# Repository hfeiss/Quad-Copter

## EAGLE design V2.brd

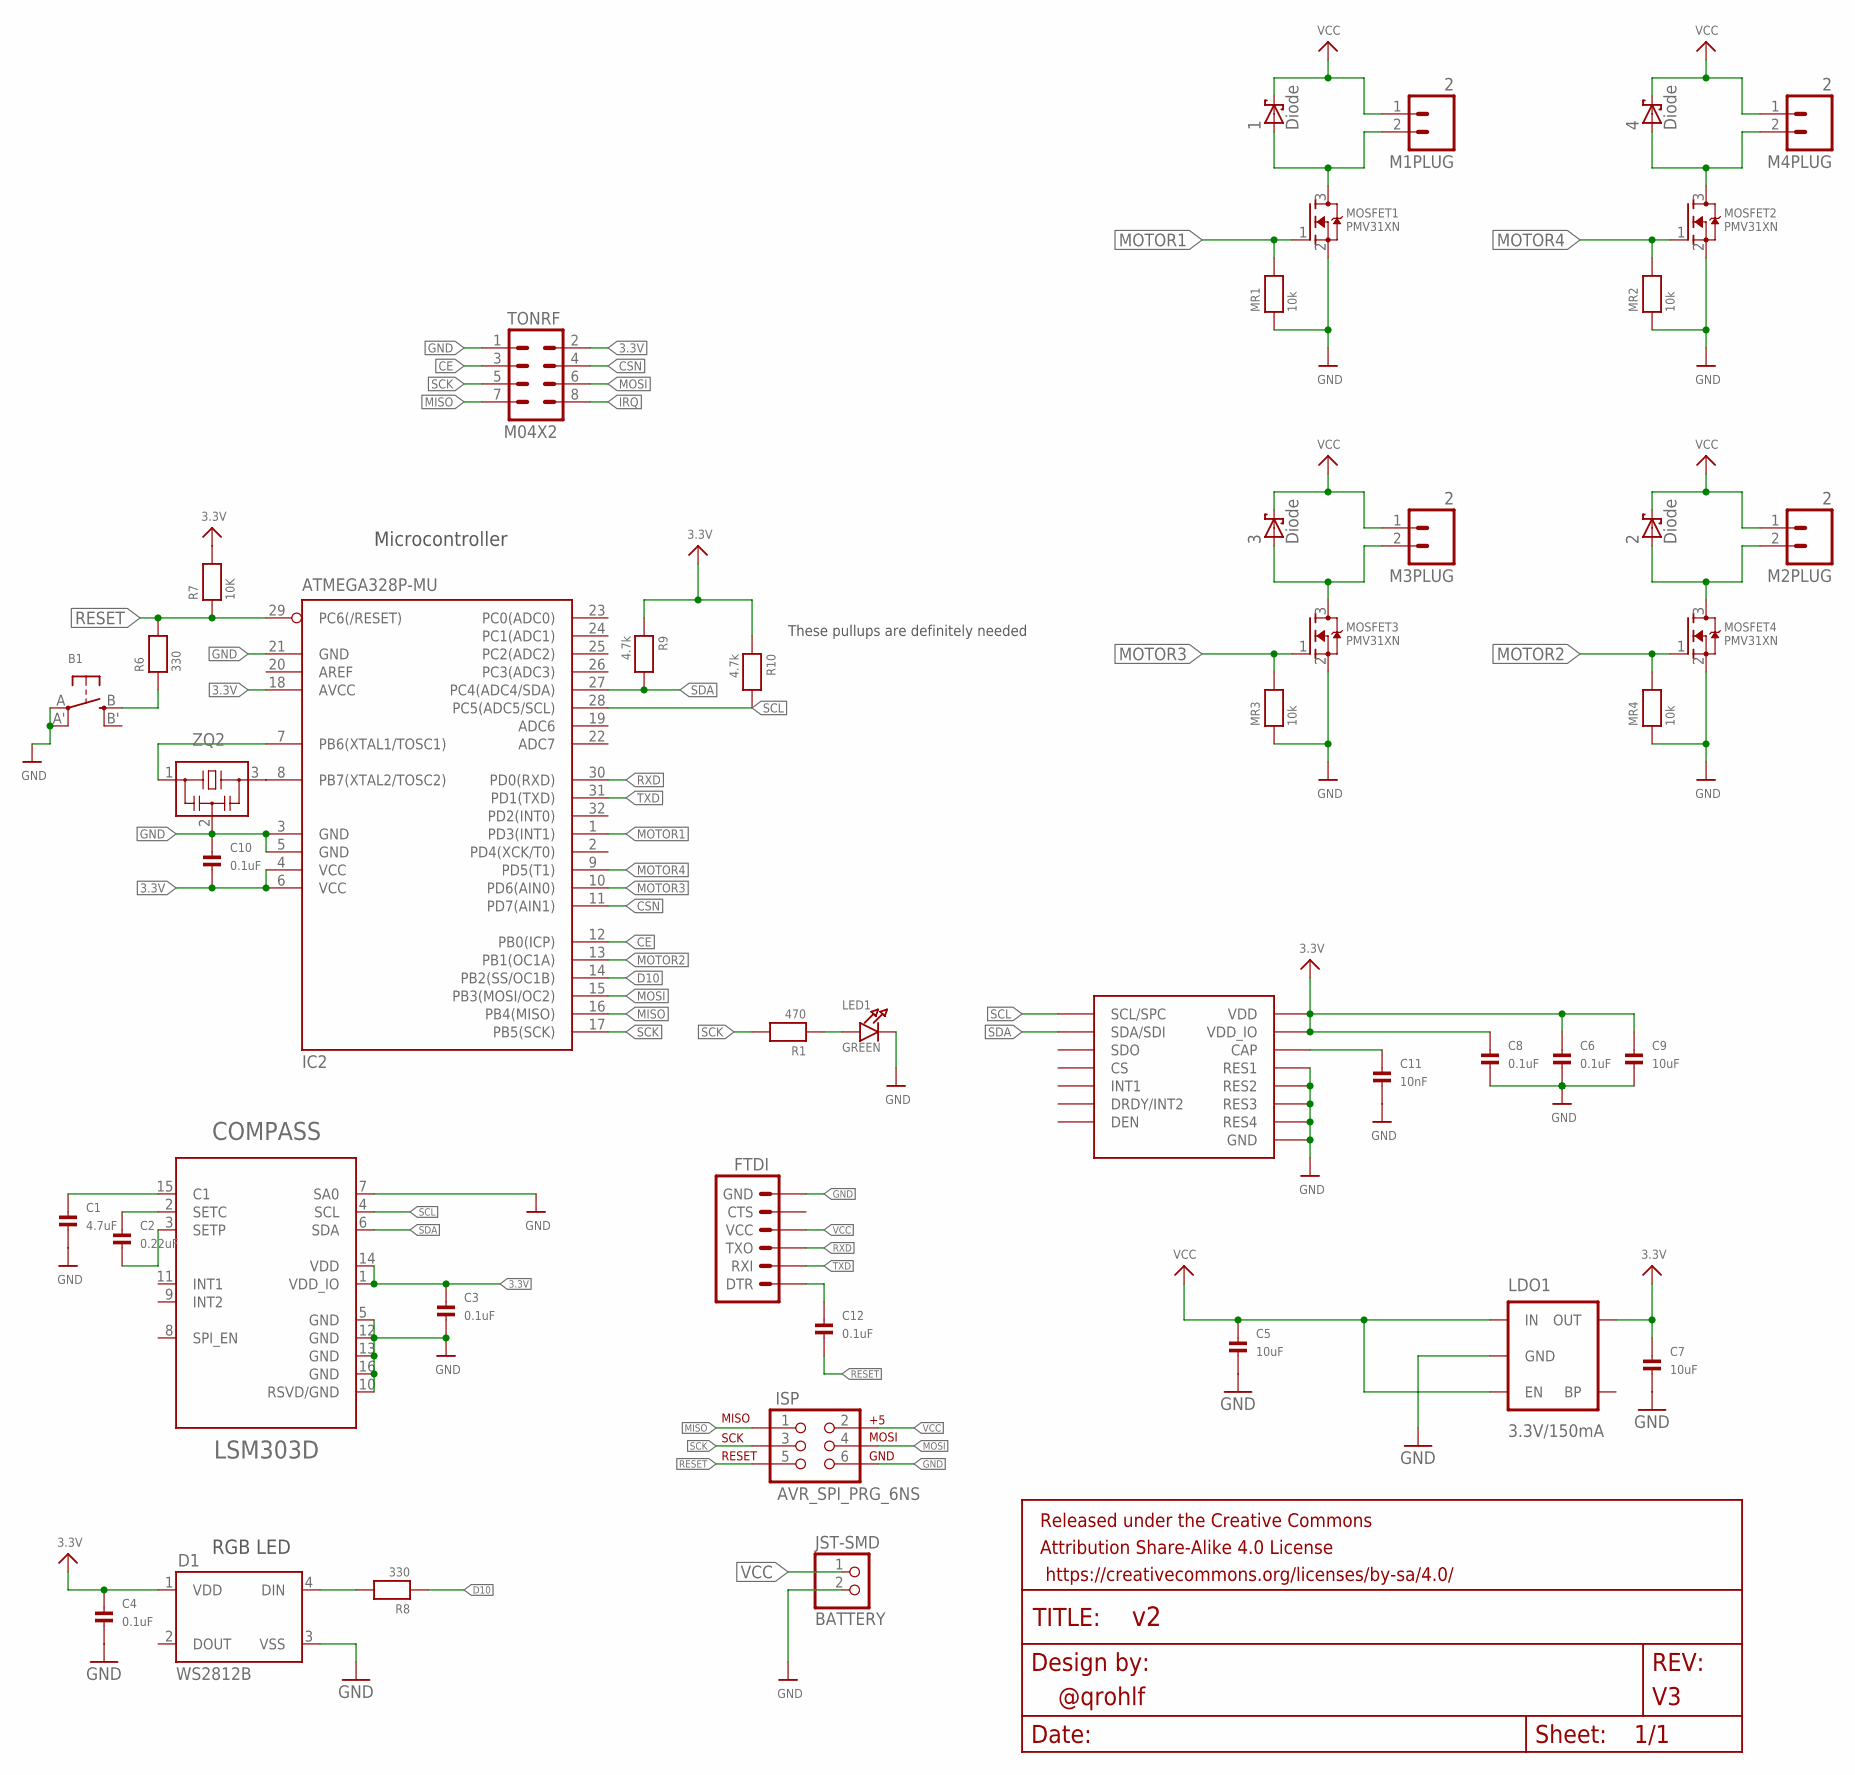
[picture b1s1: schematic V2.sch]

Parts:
1, 2, 3, 4: Diode; SOT23
B1: SWITCH_TACT_SMT4.6X2.8; BTN_KMR2_4.6X2.8
BATTERY: JST-SMD; JST-PH-2-SMT-RA
C1: 4.7uF; 0603-MINI
C2: 0.22uF; 0603-MINI
C3, C4, C6, C8, C10, C12: 0.1uF; 0603-MINI
C5, C7, C9: 10uF; 0603-MINI
C11: 10nF; 0603-MINI
COMPASS: LSM303D; LGA16_3X5
D1: WS2812B
FRAME1: >VERSION; DUMMY
FTDI: ARDUINO_SERIAL_PROGRAMLOCK; 1X06_LOCK
IC2: ATMEGA328P-MU; TQFP32-08
ISP: AVR_SPI_PRG_6NS; 2X3-NS
L3GD20H: L3GD20H; LGA16L
LDO1: 3.3V/150mA; SOT23-5
LED1: GREEN; CHIPLED_0603
M1PLUG, M2PLUG, M3PLUG, M4PLUG: 2; MOLEX-1X2_LOCK
MOSFET1, MOSFET2, MOSFET3, MOSFET4: PMV31XN; SOT23-R
MR1, MR2, MR3, MR4: 10k; 0603-MINI
R1: 470; 0603-MINI
R6, R8: 330; 0603-MINI
R7: 10K; 0603-MINI
R9, R10: 4.7k; 0603-MINI
TONRF: M04X2; 2X4
ZQ2: CSTCE8M00G52-R0; CSTCE

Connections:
3.3V: C3.1, C4.1, C6.1, C7.1, C8.1, C9.1, C10.2, COMPASS.1 (VDD_IO), COMPASS.14 (VDD), D1.1 (VDD), IC2.4 (VCC), IC2.6 (VCC), IC2.18 (AVCC), L3GD20H.P$1 (VDD_IO), L3GD20H.P$16 (VDD), LDO1.5 (OUT), R7.2, R9.1, R10.1, TONRF.2
C1: C1.1, COMPASS.15 (C1)
CE: IC2.12 (PB0(ICP)), TONRF.3
CSN: IC2.11 (PD7(AIN1)), TONRF.4
D10: IC2.14 (PB2(SS/OC1B)), R8.1
GND: B1.A, B1.A' (P1), BATTERY.2 (1), C1.2, C3.2, C4.2, C5.2, C6.2, C7.2, C8.2, C9.2, C10.1, C11.2, COMPASS.5 (GND), COMPASS.7 (SA0), COMPASS.10 (RSVD/GND), COMPASS.12 (GND), COMPASS.13 (GND), COMPASS.16 (GND), D1.3 (VSS), FTDI.6 (GND), IC2.3 (GND), IC2.5 (GND), IC2.21 (GND), ISP.6, L3GD20H.P$9 (RES1), L3GD20H.P$10 (RES2), L3GD20H.P$11 (RES3), L3GD20H.P$12 (GND), L3GD20H.P$13 (GND), L3GD20H.P$15 (RES4), LDO1.2 (GND), LED1.C, MOSFET1.2 (S), MOSFET2.2 (S), MOSFET3.2 (S), MOSFET4.2 (S), MR1.1, MR2.1, MR3.1, MR4.1, TONRF.1, ZQ2.2
IRQ: TONRF.8
MISO: IC2.16 (PB4(MISO)), ISP.1, TONRF.7
MOSI: IC2.15 (PB3(MOSI/OC2)), ISP.4, TONRF.6
MOTOR1: IC2.1 (PD3(INT1)), MOSFET1.1 (G), MR1.2
MOTOR2: IC2.13 (PB1(OC1A)), MOSFET4.1 (G), MR4.2
MOTOR3: IC2.10 (PD6(AIN0)), MOSFET3.1 (G), MR3.2
MOTOR4: IC2.9 (PD5(T1)), MOSFET2.1 (G), MR2.2
unnamed: B1.B (S), R6.1
unnamed: C12.1, FTDI.1 (DTR)
unnamed: D1.4 (DIN), R8.2
unnamed: LED1.A, R1.1
unnamed: C11.1, L3GD20H.P$14 (CAP)
unnamed: 3.1 (A), M3PLUG.2, MOSFET3.3 (D)
unnamed: 2.1 (A), M2PLUG.2, MOSFET4.3 (D)
unnamed: IC2.8 (PB7(XTAL2/TOSC2)), ZQ2.3
unnamed: IC2.7 (PB6(XTAL1/TOSC1)), ZQ2.1
unnamed: 1.1 (A), M1PLUG.2, MOSFET1.3 (D)
unnamed: 4.1 (A), M4PLUG.2, MOSFET2.3 (D)
RESET: C12.2, IC2.29 (PC6(/RESET)), ISP.5, R6.2, R7.1
RXD: FTDI.3 (TXO), IC2.30 (PD0(RXD))
SCK: IC2.17 (PB5(SCK)), ISP.3, R1.2, TONRF.5
SCL: COMPASS.4 (SCL), IC2.28 (PC5(ADC5/SCL)), L3GD20H.P$2 (SCL/SPC), R10.2
SDA: COMPASS.6 (SDA), IC2.27 (PC4(ADC4/SDA)), L3GD20H.P$3 (SDA/SDI), R9.2
SETC: C2.1, COMPASS.2 (SETC)
SETP: C2.2, COMPASS.3 (SETP)
TXD: FTDI.2 (RXI), IC2.31 (PD1(TXD))
VCC: 1.3 (C), 2.3 (C), 3.3 (C), 4.3 (C), BATTERY.1 (2), C5.1, FTDI.4 (VCC), ISP.2, LDO1.1 (IN), LDO1.3 (EN), M1PLUG.1, M2PLUG.1, M3PLUG.1, M4PLUG.1

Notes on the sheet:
Microcontroller
RGB LED
These pullups are definitely needed

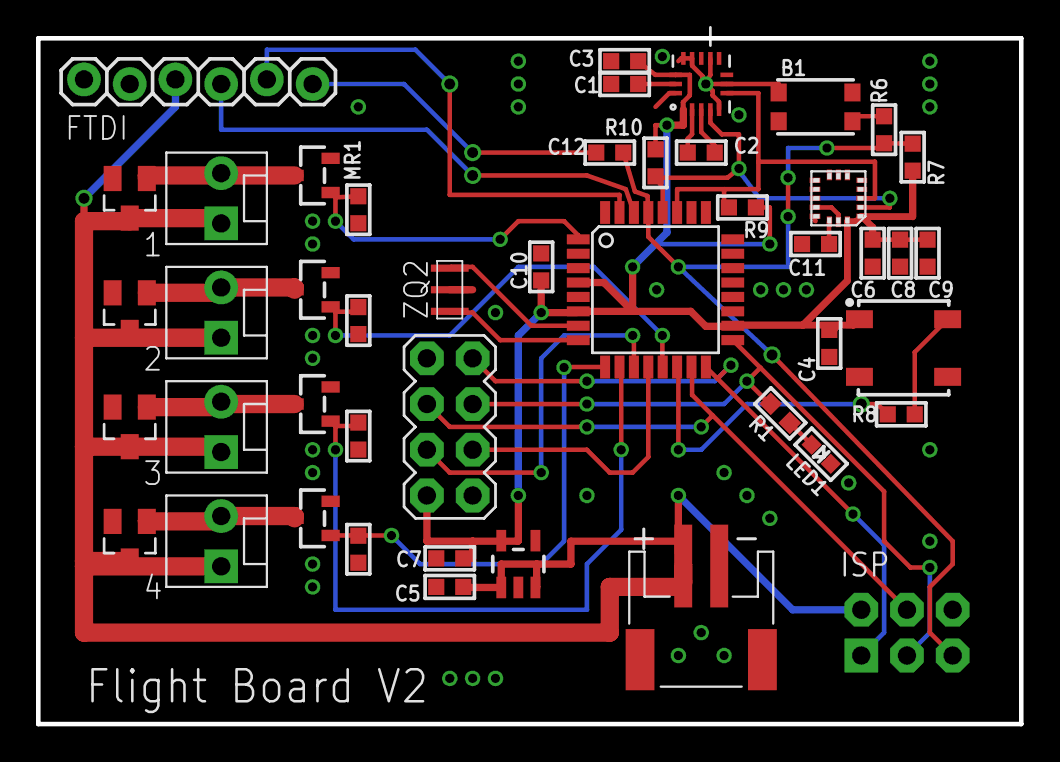
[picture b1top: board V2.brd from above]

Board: 2 copper layers, 54.6 x 38.1 mm, 47 parts (0 on the bottom side), 32 nets.

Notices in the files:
parts and their libraries:
microbuilder: This work is placed in the public domain, and may be freely used for commercial and non-commercial work with the following conditions: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
SparkFun-LED: Licensing: Creative Commons ShareAlike 4.0 International - https://creativecommons.org/licenses/by-sa/4.0
